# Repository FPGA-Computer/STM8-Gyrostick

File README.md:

# STM8 Gyrostick

This is a USB HID game controller inspired by [Cemu Gyro Joystick](https://github.com/ArsenicBismuth/Cemu-GyroStick) project. 
The hardware is based on cheap [MPU6050 modules](http://wiki.sunfounder.cc/index.php?title=MPU6050_Module) used by [Gyro_Joystick](https://github.com/ArsenicBismuth/Arduino-Programs/tree/master/Gyro_Joystick).

It uses a firmware based USB library on a STM8S003 similar to VUSB and has to live with the HID report limitations of 8 bytes for low speed devices. The 3 Accelerometers and 3 Gyroscopes are grouped logically under their own reportIDs and takes turn being sent.
There is a long list of STM8 I2C peripheral errata, so I have no choice but to base mine on ST's heavy IRQ code from [AN3281 - STM8 8-bit MCUs I2C optimized examples](https://www.st.com/en/embedded-software/stsw-stm8004.html).
A simple busy wait was all that was need to make both of them coexist.

[My project page](https://hw-by-design.blogspot.com/2021/05/stm8-gyrostock.html)

# STM8 VUSB

The firmware only USB stack is an unofficial fork from [STM8S-VUSB-KEYBOARD](https://github.com/BBS215/STM8S-VUSB-KEYBOARD)

- Works with current special edition of Cosmic C (4.4.10) and current version of STVD (4.3.12)

Note: 

The USB stack calibrates the HSI clock while connected to the PC. The calibration is store in EEPROM. It may take a couple of minutes the first time before it functions correctly.

# Licenses

Hardware
- designed by me.  License under Creative Common Attribution 4.0 International [CC BY 4.0](https://creativecommons.org/licenses/by/4.0/)

Firmware
- Code written by me: [GPL 3.0](https://www.gnu.org/licenses/gpl-3.0.en.html)

3rd party firmware used
- STM8 USB stack is under [GPL-2.0](https://www.gnu.org/licenses/old-licenses/gpl-2.0.en.html). It is based on work by [Github user BBS215](https://github.com/BBS215)
- MPU6050.h header file by Harinadha Reddy Chintalapalli <harinath.ec@gmail.com> is under [MIT license ](https://mit-license.org/)
- ST STM8 header file under "MCD-ST Liberty SW License Agreement V2" text [here](https://www.st.com/content/ccc/resource/legal/legal_agreement/license_agreement/group0/59/57/63/12/cf/a6/47/65/SLA0044/files/SLA0044.txt/jcr:content/translations/en.SLA0044.txt)
- I2C library are released as a published app. note by ST MCD Application Team. They can be used by ST STM8 customers.  I modified and cleaned up their code and not claiming copyright.

Initial release -  WIP.  Hardware working with Windows, but not picked up by Cemu software. Hard to debug the massive amount of Node.JS framework brought in by CEMU without *any* documentations

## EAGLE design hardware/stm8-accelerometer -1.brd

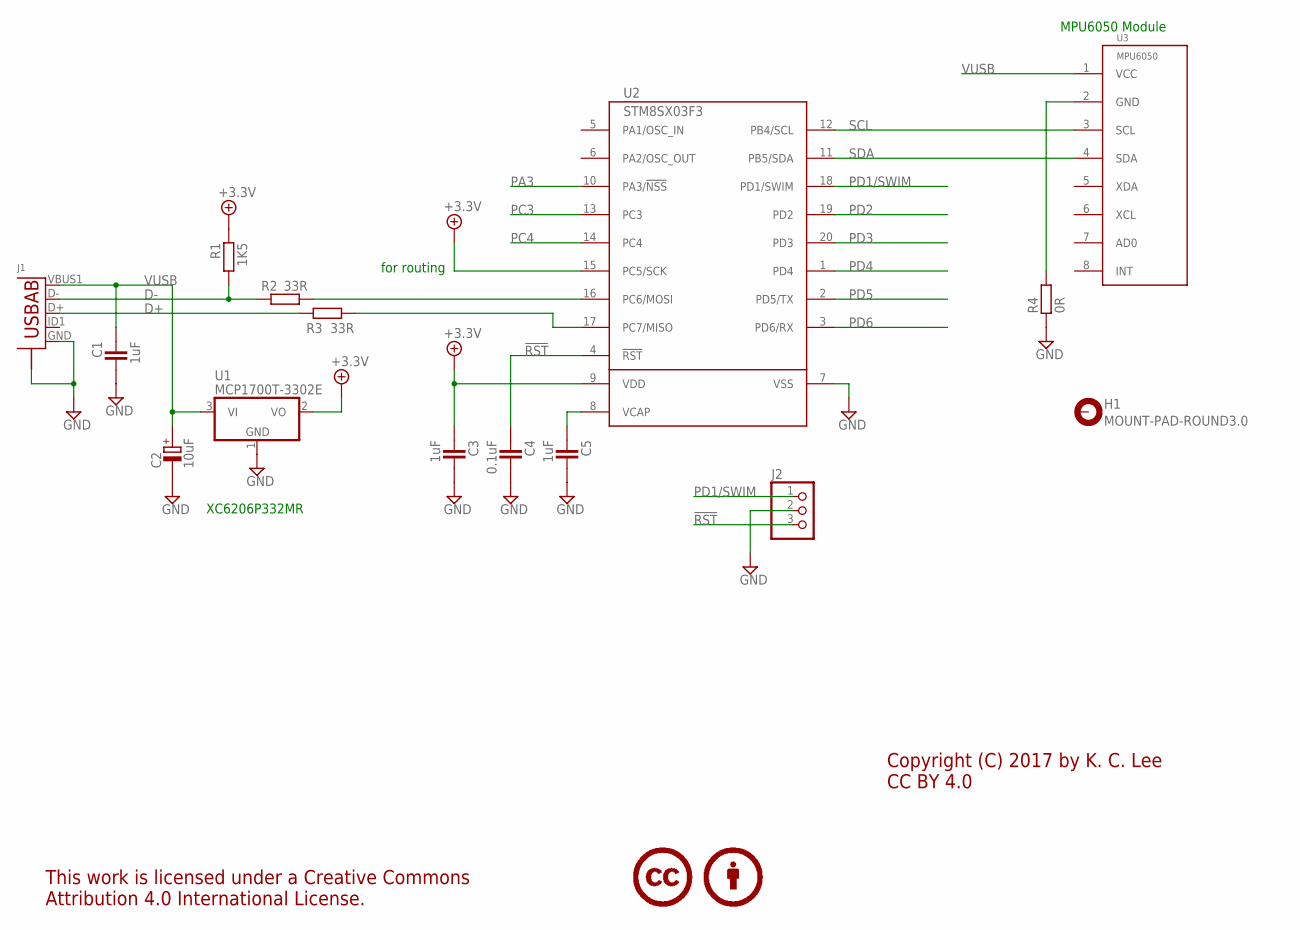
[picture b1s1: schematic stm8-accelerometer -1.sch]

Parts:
C1: 1uF; CAPC1608X92N; PARTNO NC 0805
C2: 10uF; CAPMP6032X280N; PARTNO 1uF X7R 0603
C3, C5: 1uF; CAPC1608X92N; PARTNO 1uF X7R 0603
C4: 0.1uF; CAPC1608X92N; PARTNO 1uF X7R 0603
H1: MOUNT-PAD-ROUND3.0; 3,0-PAD
J1: USB-ABBG-ORG; USB-AB-MICRO-SMD_V03_SMT
J2: PINHD-1X3_2.54; 1X03
LICENSE1: CC-BY50%; CC-BY-50
R1: 1K5; RESC1608X55N; PARTNO 1K5 0603
R2, R3: 33R; RESC1608X55N; PARTNO 47R 0603
R4: 0R; RESC3115X70N
U1: MCP1700T-3302E; SOT95P280X135-3N; PARTNO MCP1700T-3302E/TT
U2: STM8SX03F3; TSSOP20
U3: MPU6050

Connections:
!RST: C4.1, J2.3, U2.4 (!RST)
+3.3V: C3.1, R1.1, U1.2 (VO), U2.9 (VDD), U2.15 (PC5/SCK)
D+: J1.D+, R3.1
D-: J1.D-, R1.2, R2.1
GND: C1.2, C2.-, C3.2, C4.2, C5.2, J1.GND, J1.S1 (S), J1.S2 (S), J1.S3 (S), J1.S4 (S), J2.2, R4.1, U1.1 (GND), U2.7 (VSS)
unnamed: R4.2, U3.2 (GND)
unnamed: C5.1, U2.8 (VCAP)
unnamed: R3.2, U2.17 (PC7/MISO)
unnamed: R2.2, U2.16 (PC6/MOSI)
PA3: U2.10 (PA3/!NSS)
PC3: U2.13 (PC3)
PC4: U2.14 (PC4)
PD1/SWIM: J2.1, U2.18 (PD1/SWIM)
PD2: U2.19 (PD2)
PD3: U2.20 (PD3)
PD4: U2.1 (PD4)
PD5: U2.2 (PD5/TX)
PD6: U2.3 (PD6/RX)
SCL: U2.12 (PB4/SCL), U3.3 (SCL)
SDA: U2.11 (PB5/SDA), U3.4 (SDA)
VUSB: C1.1, C2.+, J1.VBUS1 (VBUS), U1.3 (VI), U3.1 (VCC)

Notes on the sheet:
Copyright (C) 2017 by K. C. Lee CC BY 4.0
XC6206P332MR
for routing
MPU6050 Module

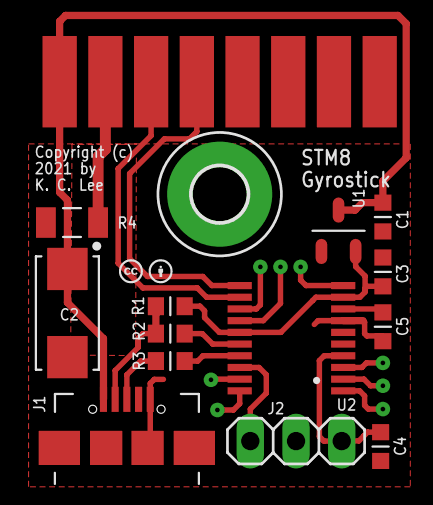
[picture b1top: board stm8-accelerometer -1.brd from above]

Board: 2 copper layers, 16 parts (0 on the bottom side), 13 nets.

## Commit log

2021-05-13 first commit - firmware is WIP upload later
2021-05-13 fix up
2021-05-13 initial firmware upload
2021-05-13 clean up
2021-05-15 Clean up. Still WIP
2021-05-15 forgot that #include for main.h"
2021-05-15 Add sketchup 3D model of PCB assembly
2021-05-15 Add sketchup 3D model of PCB assembly (PNG sample)

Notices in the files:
parts and their libraries:
Misc logo: This work is licensed under a Creative Commons
Attribution 4.0 International License.
